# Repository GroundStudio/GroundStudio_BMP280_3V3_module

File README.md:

GroundStudio BMP280 3V3 module
====================================

Get it from [ardushop.ro](https://ardushop.ro/ro/home/2512-modul-senzor-presiune-atmosferica-bmp280-3v3-groundstudio.html)

Explore all the GroundStudio products at [GroundStudio.ro](https://groundstudio.ro/)

Description
-------------------
Barometric pressure and temperature sensor module based on BMP280 chip.

Contents
-------------------

* [/Documentation](https://github.com/GroundStudio/GroundStudio_BMP280_3V3_module/tree/main/Documentation) -- Contains documentation written during creation of this repository, with readme.md index of its own!
* [/Firmware](https://github.com/GroundStudio/GroundStudio_BMP280_3V3_module/tree/main/Firmware) -- Firmware (bootloaders, etc)
* [/Hardware](https://github.com/GroundStudio/GroundStudio_BMP280_3V3_module/tree/main/Hardware) -- Schematics, layout.
* [/Libraries](https://github.com/GroundStudio/GroundStudio_BMP280_3V3_module/tree/main/Libraries) -- Arduino/CircuitPython libraries. 
* [/Tools](https://github.com/GroundStudio/GroundStudio_BMP280_3V3_module/tree/main) -- Tools needed for compiling, uploading bootloader, etc.

Versions
-------------------
*(Not all tags shown)*
* [V0.2] Initial version

License
-------------------
This is released under the [Attribution-ShareAlike 4.0 International (CC BY-SA 4.0)](https://creativecommons.org/licenses/by-sa/4.0/) license. 
**You are welcome to use this for commercial purposes.**

Please consider contributing back to this project or others to help the open-source hardware community continue to thrive and grow! 

Certifications:

[Open Source Hardware Association](https://certification.oshwa.org/ro000017.html)   
   
[
](https://certification.oshwa.org/ro000017.html)

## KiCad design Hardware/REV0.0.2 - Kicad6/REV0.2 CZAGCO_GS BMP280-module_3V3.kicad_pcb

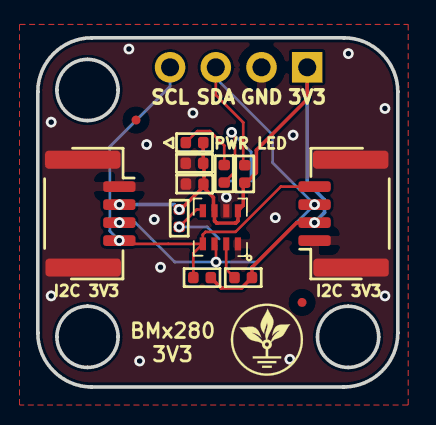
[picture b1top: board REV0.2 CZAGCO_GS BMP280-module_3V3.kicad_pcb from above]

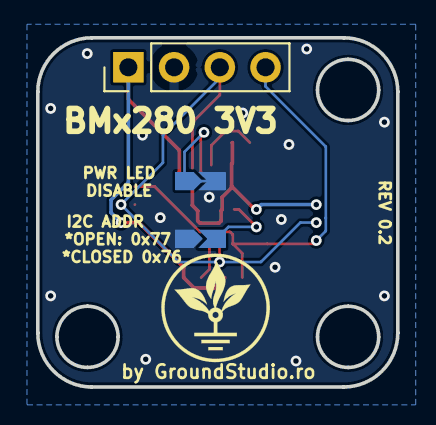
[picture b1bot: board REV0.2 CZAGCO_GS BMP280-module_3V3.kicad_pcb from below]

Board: 2 copper layers, 20.0 x 19.4 mm, 14 parts (3 on the bottom side), 8 nets.

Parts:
C1: 100nF; C_0402_1005Metric
C2: 1uF; C_0402_1005Metric
D1: RED; LED_0402_1005Metric
J1: Conn_01x04; PinHeader_1x04_P2.54mm_Vertical_Male
J2: PWR LED DISABLE; SolderJumper_NC
J4: I2C ADDR SELECT; SolderJumper_NO
R1, R2, R3, R4: 10K; R_0402_1005Metric
R5: 1k; R_0402_1005Metric
U1: BMP280; LGA-8_2x2.5mm_BMP&BME280
X1, X2: i2c_3V3; SH__1x04_P1.00mm_Horizontal

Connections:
+3V3: C1.1, C2.1, D1.2, J1.1, R1.1, R2.1, R3.2, R4.1, U1.6, U1.8, X1.2, X2.2
ADDR: J4.2, R3.1, U1.5
CSB: R1.2, U1.2
GND: C1.2, C2.2, J1.2, J2.2, J4.1, U1.1, U1.7, X1.0, X1.1, X2.0, X2.1
unnamed: D1.1, R5.1
unnamed: J2.1, R5.2
SCK: J1.4, R2.2, U1.4, X1.4, X2.4
SDA: J1.3, R4.2, U1.3, X1.3, X2.3

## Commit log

2023-10-23 - first commit
2023-10-23 - initial commit
2023-10-25 - added datasheet
